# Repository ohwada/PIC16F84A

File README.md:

PIC16F84A
===============

MIcrochip - 8 bit Microcontroller<br>
http://ww1.microchip.com/downloads/en/DeviceDoc/35007b.pdf

### LED
https://github.com/ohwada/PIC16F84A/tree/master/docs/led <br>

* LED Blink <br>

### Base
https://github.com/ohwada/PIC16F84A/tree/master/docs/base <br>

* blink LED with timer interrupt <br>
* play Doe Ray Me with buzzer tone <br>
* play Koinobori song with buzzer tone <br>

### Slot
https://github.com/ohwada/PIC16F84A/tree/master/docs/slot <br>

* 7 Seg LED <br>
* Slot Game <br>

### PICkit3
https://github.com/ohwada/PIC16F84A/tree/master/docs/pickit3 <br>

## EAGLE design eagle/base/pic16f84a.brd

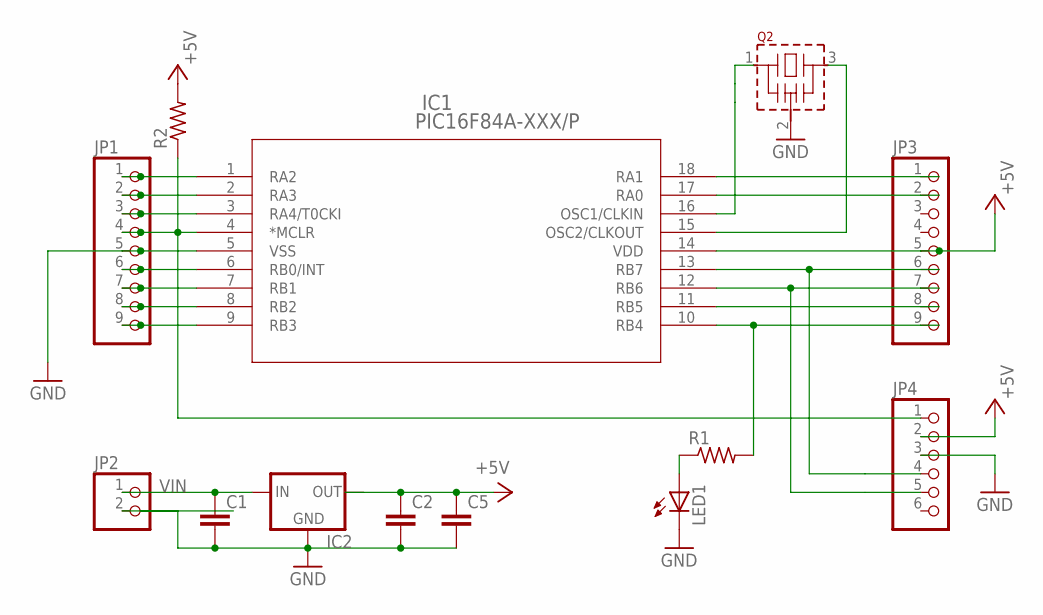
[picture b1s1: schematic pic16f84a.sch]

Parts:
C1, C2, C5: C-EU050-025X075; C050-025X075
IC1: PIC16F84A-XXX/P; PDIP18_300MC
IC2: 78XXS
JP1, JP3: PINHD-1X9; 1X09
JP2: PINHD-1X2; 1X02
JP4: PINHD-1X6; 1X06
LED1: LED3MM
Q2: CSTLS_X
R1, R2: R-US_0207/10; 0207/10

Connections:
+5V: C2.1, C5.1, IC1.14 (VDD), IC2.OUT, JP3.5, JP4.2, R2.2
GND: C1.2, C2.2, C5.2, IC1.5 (VSS), IC2.GND, JP1.5, JP2.2, JP4.3, LED1.K (C), Q2.2 (VSS)
unnamed: IC1.1 (RA2), JP1.1
unnamed: IC1.2 (RA3), JP1.2
unnamed: IC1.3 (RA4/T0CKI), JP1.3
unnamed: IC1.4 (*MCLR), JP1.4, JP4.1, R2.1
unnamed: IC1.15 (OSC2/CLKOUT), Q2.3
unnamed: IC1.6 (RB0/INT), JP1.6
unnamed: IC1.7 (RB1), JP1.7
unnamed: IC1.8 (RB2), JP1.8
unnamed: IC1.9 (RB3), JP1.9
unnamed: IC1.18 (RA1), JP3.1
unnamed: IC1.17 (RA0), JP3.2
unnamed: IC1.12 (RB6), JP3.7, JP4.5
unnamed: LED1.A, R1.1
unnamed: IC1.13 (RB7), JP3.6, JP4.4
unnamed: IC1.11 (RB5), JP3.8
unnamed: IC1.10 (RB4), JP3.9, R1.2
unnamed: IC1.16 (OSC1/CLKIN), Q2.1
VIN: C1.1, IC2.IN, JP2.1

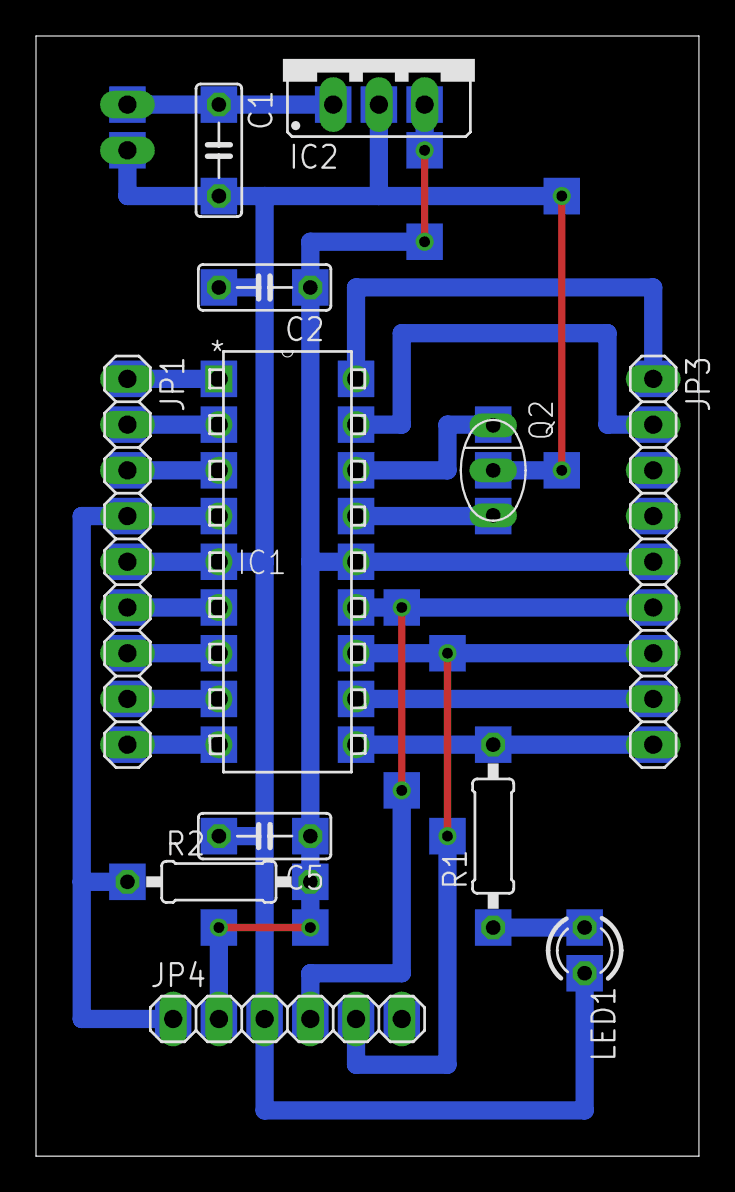
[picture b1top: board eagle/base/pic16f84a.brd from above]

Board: 2 copper layers, 36.8 x 62.2 mm, 13 parts (1 on the bottom side), 20 nets.

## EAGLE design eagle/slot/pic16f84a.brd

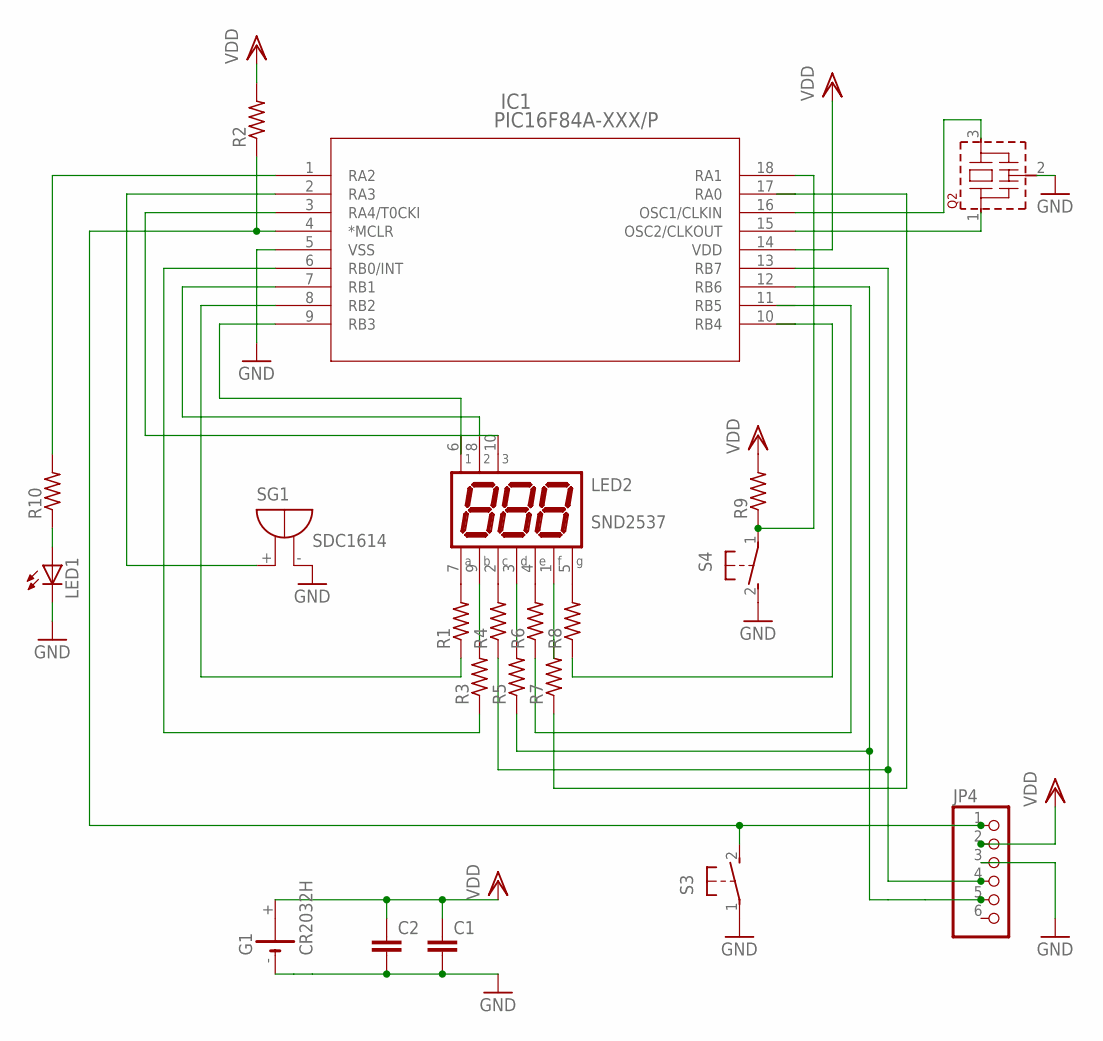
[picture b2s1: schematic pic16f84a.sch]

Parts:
C1, C2: C-EU050-025X075; C050-025X075
G1: CR2032H
IC1: PIC16F84A-XXX/P; PDIP18_300MC
JP4: PINHD-1X6; 1X06
LED1: LED3MM
LED2: SND2537; SND2537-PKG
Q2: CSTLS_X
R1, R2, R3, R4, R5, R6, R7, R8, R9, R10: R-US_0207/10; 0207/10
S3, S4: 31-XX; B3F-31XX
SG1: SDC1614

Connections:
GND: C1.2, C2.2, G1.-, IC1.5 (VSS), JP4.3, LED1.K (C), Q2.2 (VSS), S3.1, S4.2 (S), SG1.-
unnamed: IC1.13 (RB7), JP4.4, R4.1
unnamed: IC1.3 (RA4/T0CKI), LED2.10 (3)
unnamed: IC1.10 (RB4), R8.1
unnamed: IC1.15 (OSC2/CLKOUT), Q2.1
unnamed: IC1.8 (RB2), R1.1
unnamed: IC1.2 (RA3), SG1.+
unnamed: IC1.18 (RA1), R9.1, S4.1
unnamed: IC1.11 (RB5), R6.1
unnamed: IC1.1 (RA2), R10.2
unnamed: IC1.17 (RA0), R7.1
unnamed: IC1.12 (RB6), JP4.5, R5.1
unnamed: LED2.7 (A), R1.2
unnamed: LED2.9 (B), R3.2
unnamed: LED2.2 (C), R4.2
unnamed: LED1.A, R10.1
unnamed: IC1.9 (RB3), LED2.6 (1)
unnamed: LED2.3 (D), R5.2
unnamed: LED2.4 (E), R6.2
unnamed: LED2.1 (F), R7.2
unnamed: LED2.5 (G), R8.2
unnamed: IC1.16 (OSC1/CLKIN), Q2.3
unnamed: IC1.7 (RB1), LED2.8 (2)
unnamed: IC1.6 (RB0/INT), R3.1
unnamed: IC1.4 (*MCLR), JP4.1, R2.1, S3.2 (S)
VDD: C1.1, C2.1, G1.+, IC1.14 (VDD), JP4.2, R2.2, R9.2

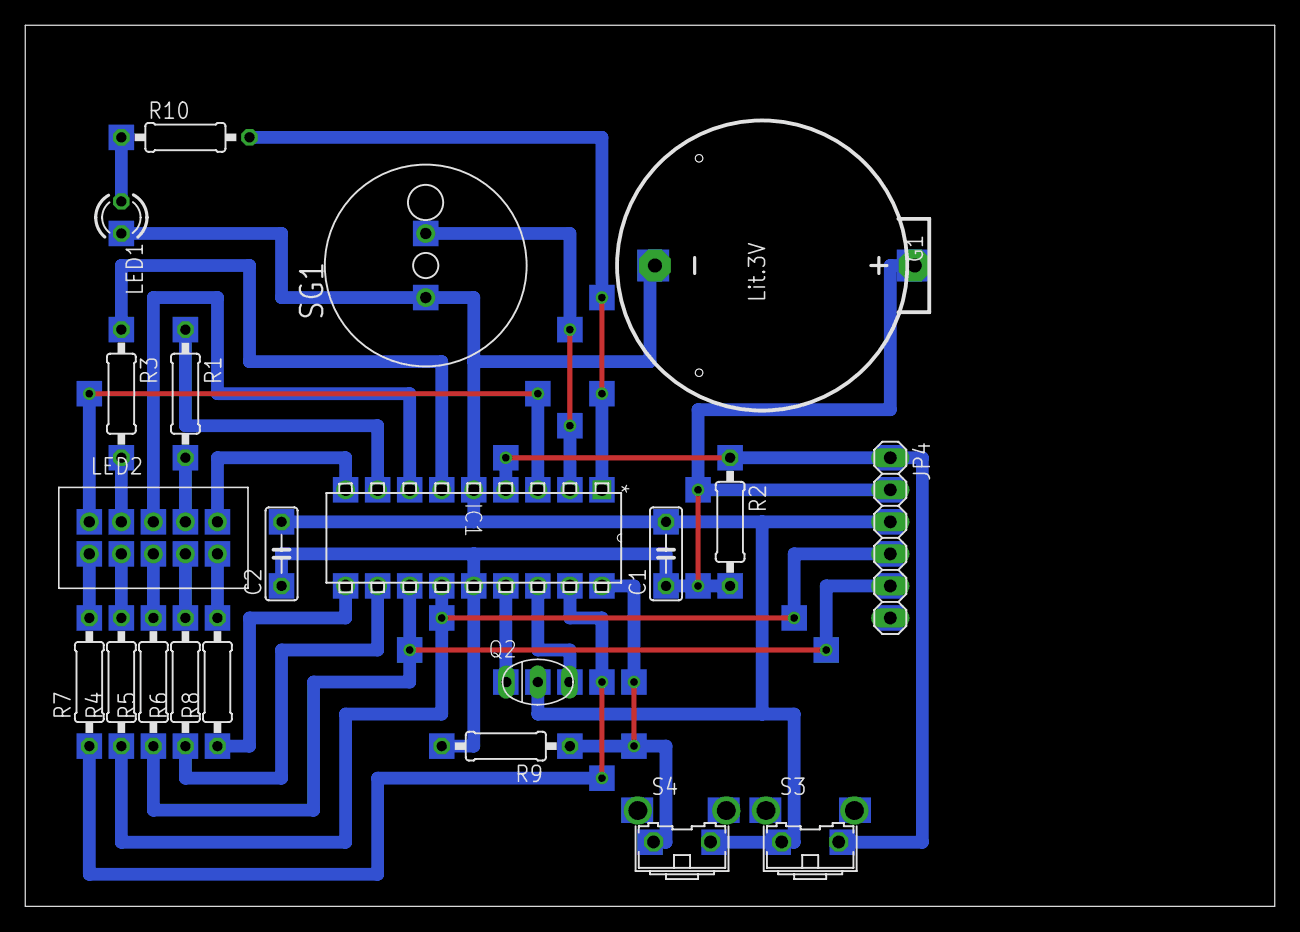
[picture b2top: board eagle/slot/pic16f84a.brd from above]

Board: 2 copper layers, 99.1 x 69.8 mm, 21 parts (0 on the bottom side), 26 nets.

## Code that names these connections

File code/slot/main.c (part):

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/**
 * OPTION_REG
 *   7: RBPU: PORTB Pull-up Enable bit: enabled
 *   6: INTEDG: Interrupt Edge Select bit: falling edge of RB0/INT pin
 *   5: T0CS: TMR0 Clock Source Select bit: Internal instruction cycle clock
 *   4: T0SE: TMR0 Source Edge Select bit: low-to-high transition on RA4/T0CKI pin
 *   3: PSA: Prescaler Assignment bit: Timer0
 *   2-0: PS2-0: Prescaler Rate Select bits: 
 *      000 1/2,   001 1/4,    010 1/8,     011 1/16
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        PORTAbits.RA3 = is_buzzer_on;   // Buzzer
        is_buzzer_on = !is_buzzer_on;
    } else {
        PORTAbits.RA3 = 0;   // Buzzer
    }

    // --- 7 seg ---
    // turn off 7seg
    PORTBbits.RB3 = 0;
    PORTBbits.RB1 = 0;
    PORTAbits.RA4 = 0;

    // blank mode
    if ( !is_7seg_on ) return;
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
// 7Seg : RB2 RB0 RB7 RB6 RB5 RA0 RB4
    if ( PAT[n+0] == 1 ) {
        PORTBbits.RB2 = 0;
    } else {
        PORTBbits.RB2 = 1;
    }
    if ( PAT[n+1] == 1 ) {
        PORTBbits.RB0 = 0;
    } else {
        PORTBbits.RB0 = 1;
    }
    if ( PAT[n+2] == 1 ) {
        PORTBbits.RB7 = 0;
    } else {
        PORTBbits.RB7 = 1;
    }
    if ( PAT[n+3] == 1 ) {
        PORTBbits.RB6 = 0;
    } else {
        PORTBbits.RB6 = 1;
    }
    if ( PAT[n+4] == 1 ) {
        PORTBbits.RB5 = 0;
    } else {
        PORTBbits.RB5 = 1;
    }
    if ( PAT[n+5] == 1 ) {
        PORTAbits.RA0 = 0;
    } else {
        PORTAbits.RA0 = 1;
    }
    if ( PAT[n+6] == 1 ) {
        PORTBbits.RB4 = 0;
    } else {
        PORTBbits.RB4 = 1;
    }

// Anode : RB3 RB1 RA4
    if ( row_cnt == 0 ) {
        PORTBbits.RB3 = 1;
        PORTBbits.RB1 = 0;
        PORTAbits.RA4 = 0;
    } else if ( row_cnt == 1 ) {
        PORTBbits.RB3 = 0;
        PORTBbits.RB1 = 1;
        PORTAbits.RA4 = 0;
    } else if ( row_cnt == 2 ) {
        PORTBbits.RB3 = 0;
        PORTBbits.RB1 = 0;
        PORTAbits.RA4 = 1;
    }
}	

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
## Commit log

2015-04-27 FirstVersion
2015-04-27 First Version
2015-05-07 base & slot
2015-05-07 docs
2015-05-21 slot
